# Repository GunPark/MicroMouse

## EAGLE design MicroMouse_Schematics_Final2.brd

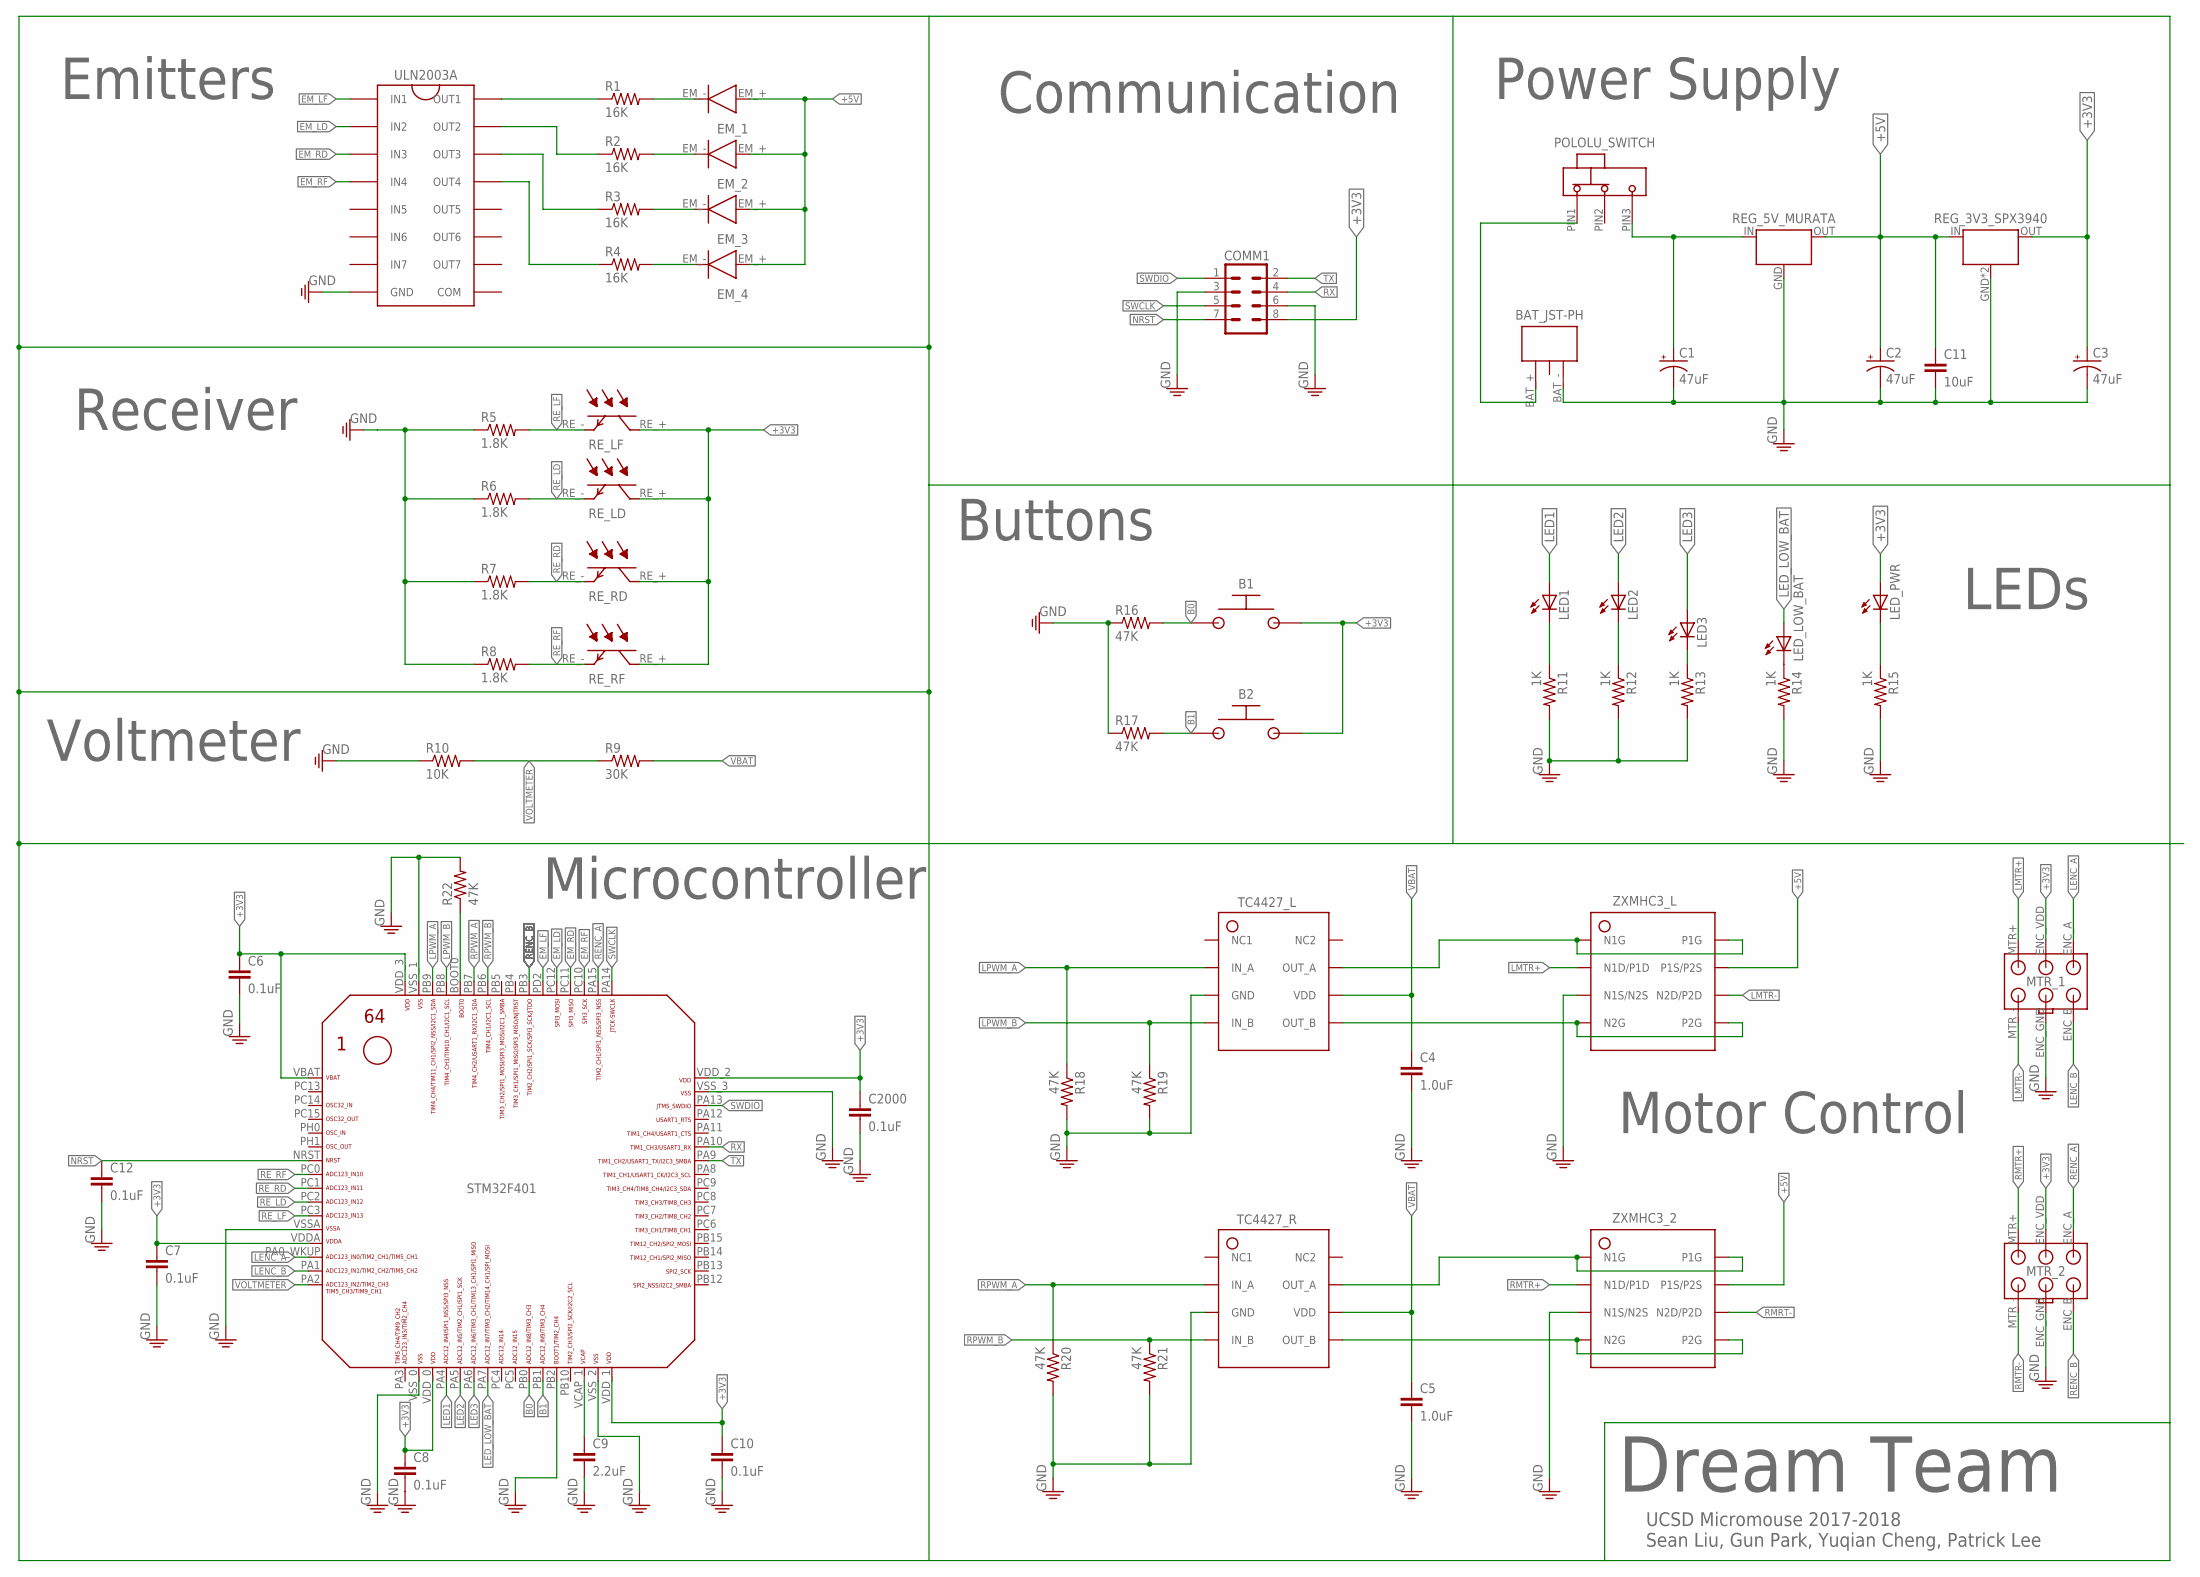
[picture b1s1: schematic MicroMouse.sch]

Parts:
B1, B2: POLOLU_BUTTON
BAT_JST-PH: 3PIN; B3B-PH-K-S
C1, C2, C3: 47uF; CAP_TANT_1210IN_3528MM
C4, C5: 1.0uF; 0805
C6, C7, C8, C10, C12, C2000: 0.1uF; 0805
C9: 2.2uF; 0805
C11: 10uF; 0805
COMM1: M04X2; 2X4
EM_1, EM_2, EM_3, EM_4: SFH4545; EMITTER
LED1, LED2, LED3: LED; LED-0805
LED_LOW_BAT: LED; LED-0805
LED_PWR: LED; LED-0805
MTR_1, MTR_2: MOTOR_ENCODER_HEADER
POLOLU_SWITCH: POLOLU_SWITCH
R1, R2, R3, R4: 16K; 0805
R5, R6, R7, R8: 1.8K; 0805
R9: 30K; 0805
R10: 10K; 0805
R11, R12, R13, R14, R15: 1K; 0805
R16, R17, R18, R19, R20, R21, R22: 47K; 0805
REG_3V3_SPX3940: 3V3_REG; SOT223
REG_5V_MURATA: REG_5V_MURATA; 5V_REG_MURATA
RE_LD: TEFT4300; RECEIVER
RE_LF: TEFT4300; RECEIVER
RE_RD: TEFT4300; RECEIVER
RE_RF: TEFT4300; RECEIVER
STM32F401: STM32F4_401_410_411_412_413_446; LQFP64
TC4427_L, TC4427_R: TC4427_SOIC8
ULN2003A: ULN2003A
ZXMHC3_2, ZXMHC3_L: ZXMHC3

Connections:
+3V3: B1.P$2 (2), B2.P$2 (2), C3.A (+), C6.1, C7.1, C8.1, C10.1, C2000.1, COMM1.8, LED_PWR.A, MTR_1.ENC_VDD, MTR_2.ENC_VDD, REG_3V3_SPX3940.OUT, RE_LD.RE_+ (C), RE_LF.RE_+ (C), RE_RD.RE_+ (C), RE_RF.RE_+ (C), STM32F401.VBAT, STM32F401.VDDA, STM32F401.VDD_0, STM32F401.VDD_1, STM32F401.VDD_2, STM32F401.VDD_3
+5V: C2.A (+), C11.1, EM_1.EM_+ (+), EM_2.EM_+ (+), EM_3.EM_+ (+), EM_4.EM_+ (+), REG_3V3_SPX3940.IN, REG_5V_MURATA.OUT, ZXMHC3_2.P1S/P2S, ZXMHC3_L.P1S/P2S
B0: B1.P$1 (1), R16.2, STM32F401.PB0
B1: B2.P$1 (1), R17.2, STM32F401.PB1
EM_LD: STM32F401.PC12, ULN2003A.2B (IN2)
EM_LF: STM32F401.PD2, ULN2003A.1B (IN1)
EM_RD: STM32F401.PC11, ULN2003A.3B (IN3)
EM_RF: STM32F401.PC10, ULN2003A.4B (IN4)
LED1: LED1.A, STM32F401.PA4
LED2: LED2.A, STM32F401.PA5
LED3: LED3.A, STM32F401.PA6
LED_LOW_BAT: LED_LOW_BAT.A, STM32F401.PA7
LENC_A: MTR_1.ENC_A, STM32F401.PA0_WKUP (PA0_AKUP)
LENC_B: MTR_1.ENC_B, STM32F401.PA1
LMTR+: MTR_1.MTR+ (MTR_+), ZXMHC3_L.N1D/P1D
LMTR-: MTR_1.MTR_-, ZXMHC3_L.N2D/P2D
LPWM_A: R18.1, STM32F401.PB9, TC4427_L.IN_A
LPWM_B: R19.1, STM32F401.PB8, TC4427_L.IN_B
unnamed: BAT_JST-PH.BAT_+, POLOLU_SWITCH.PIN1
unnamed: C1.A (+), POLOLU_SWITCH.PIN3, REG_5V_MURATA.IN
unnamed: LED1.C, R11.1
unnamed: LED2.C, R12.1
unnamed: LED3.C, R13.1
unnamed: R1.1, ULN2003A.1C (OUT1)
unnamed: LED_LOW_BAT.C, R14.1
unnamed: R2.1, ULN2003A.2C (OUT2)
unnamed: LED_PWR.C, R15.1
unnamed: R3.1, ULN2003A.3C (OUT3)
unnamed: TC4427_L.OUT_A, ZXMHC3_L.N1G, ZXMHC3_L.P1G
unnamed: R4.1, ULN2003A.4C (OUT4)
unnamed: EM_1.EM_- (-), R1.2
unnamed: TC4427_L.OUT_B, ZXMHC3_L.N2G, ZXMHC3_L.P2G
unnamed: EM_2.EM_- (-), R2.2
unnamed: EM_3.EM_- (-), R3.2
unnamed: EM_4.EM_- (-), R4.2
unnamed: TC4427_R.OUT_A, ZXMHC3_2.N1G, ZXMHC3_2.P1G
unnamed: TC4427_R.OUT_B, ZXMHC3_2.N2G, ZXMHC3_2.P2G
unnamed: C9.1, STM32F401.VCAP_1 (PB11)
unnamed: R22.1, STM32F401.BOOT0
NRST: C12.1, COMM1.7, STM32F401.NRST
RENC_A: MTR_2.ENC_A, STM32F401.PA15
RENC_B: MTR_2.ENC_B, STM32F401.PB3
RE_LD: R6.2, RE_LD.RE_- (E), STM32F401.PC2
RE_LF: R5.2, RE_LF.RE_- (E), STM32F401.PC3
RE_RD: R7.2, RE_RD.RE_- (E), STM32F401.PC1
RE_RF: R8.2, RE_RF.RE_- (E), STM32F401.PC0
RMRT-: ZXMHC3_2.N2D/P2D
RMTR+: MTR_2.MTR+ (MTR_+), ZXMHC3_2.N1D/P1D
RMTR-: MTR_2.MTR_-
RPWM_A: R20.1, STM32F401.PB7, TC4427_R.IN_A
RPWM_B: R21.1, STM32F401.PB6, TC4427_R.IN_B
RX: COMM1.4, STM32F401.PA10
SWCLK: COMM1.5, STM32F401.PA14
SWDIO: COMM1.1, STM32F401.PA13
TX: COMM1.2, STM32F401.PA9
VBAT: C4.1, C5.1, R9.2, TC4427_L.VDD, TC4427_R.VDD
VCAP_1: STM32F401.VSS_2 (VCAP_1)
VCAP_2: STM32F401.VSS_3 (VCAP_2)
VOLTMETER: R9.1, R10.2, STM32F401.PA2
VSS_0: STM32F401.VSS_0

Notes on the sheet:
Power Supply
LEDs
Communication
Motor Control
Emitters
Receiver
Voltmeter
Microcontroller
Buttons
Dream Team
UCSD Micromouse 2017-2018 Sean Liu, Gun Park, Yuqian Cheng, Patrick Lee

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
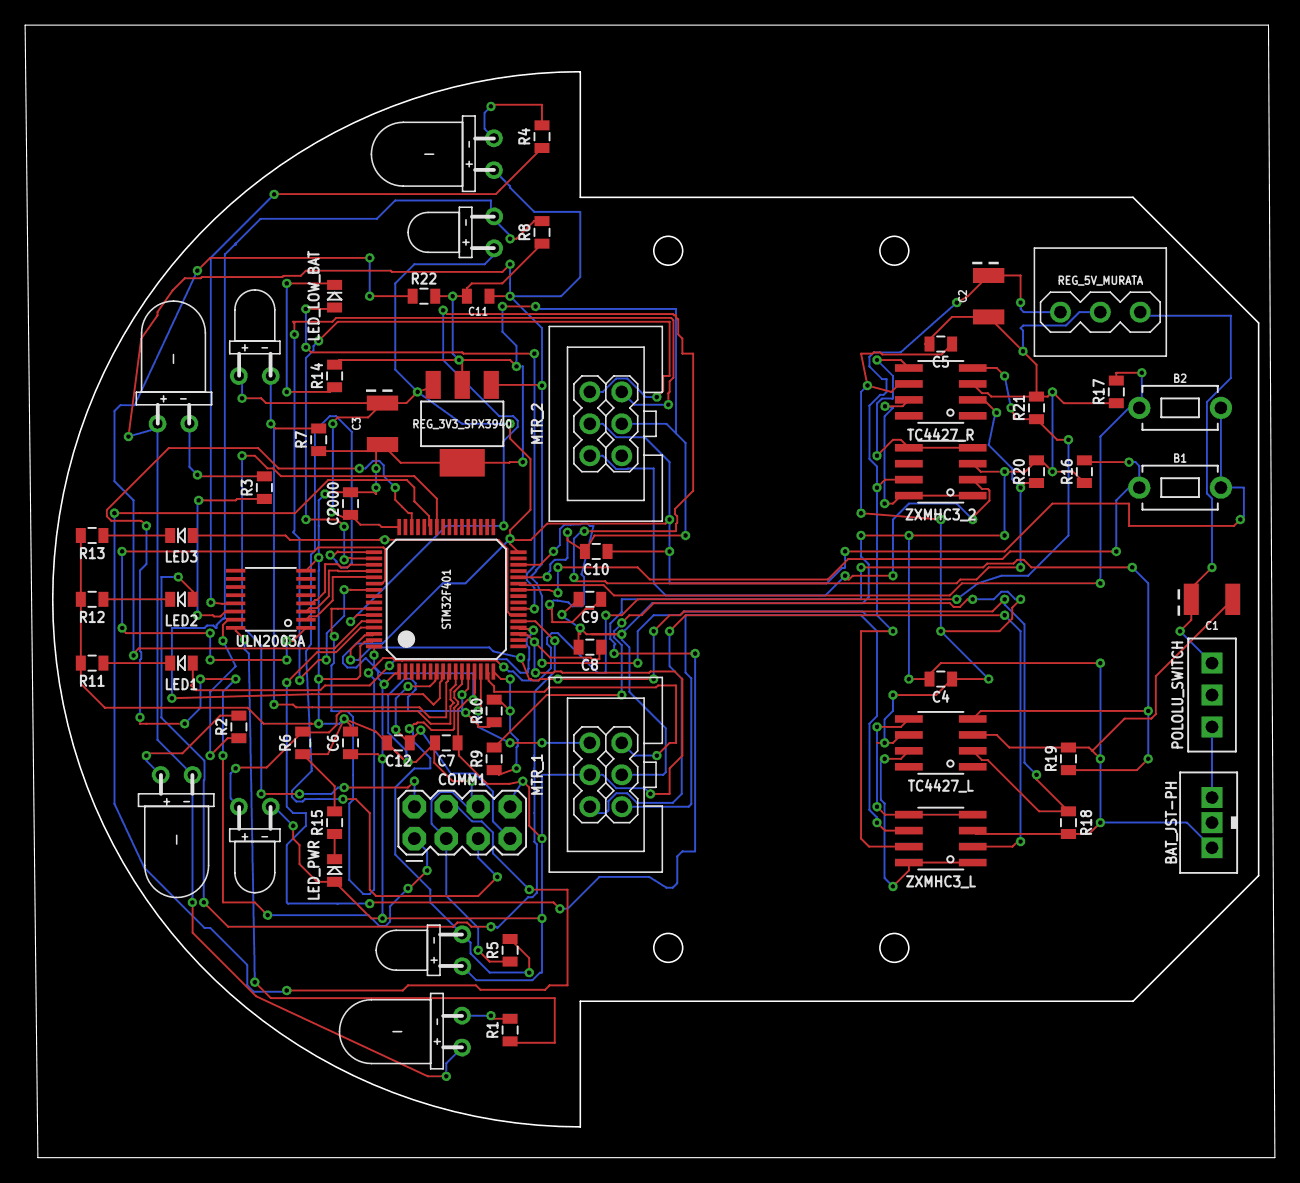
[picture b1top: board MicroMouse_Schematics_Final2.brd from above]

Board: 2 copper layers, 99.5 x 90.2 mm, 64 parts (0 on the bottom side), 57 nets.

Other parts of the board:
E$1: MOUSE_OUTLINE_2WHEEL

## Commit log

2018-02-08 Final Schematics
2018-02-12 Add files via upload
    Everything on Board (parts to be placed)
2018-02-13 Correct File
2018-02-19 Changed 47uF capacitor
2018-03-28 GND Pin & Autoroute
2018-03-30 Rough Draft 1
2018-03-31 Final Board
2018-03-31 Final Board2 (less interference with stm)
2018-03-31 Final Board (motor on top)
2018-03-31 No motor mount bs
2018-04-01 Fixed error
2018-04-01 Bottoms up
2018-04-01 Bottoms
2018-04-01 Final Fixed Board
2018-04-06 Finalized & Ordered PCB with Garber Files
2018-04-06 Garber File for Fabrication

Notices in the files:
parts and their libraries:
SparkFun-Capacitors: Licensing: Creative Commons ShareAlike 4.0 International - https://creativecommons.org/licenses/by-sa/4.0
